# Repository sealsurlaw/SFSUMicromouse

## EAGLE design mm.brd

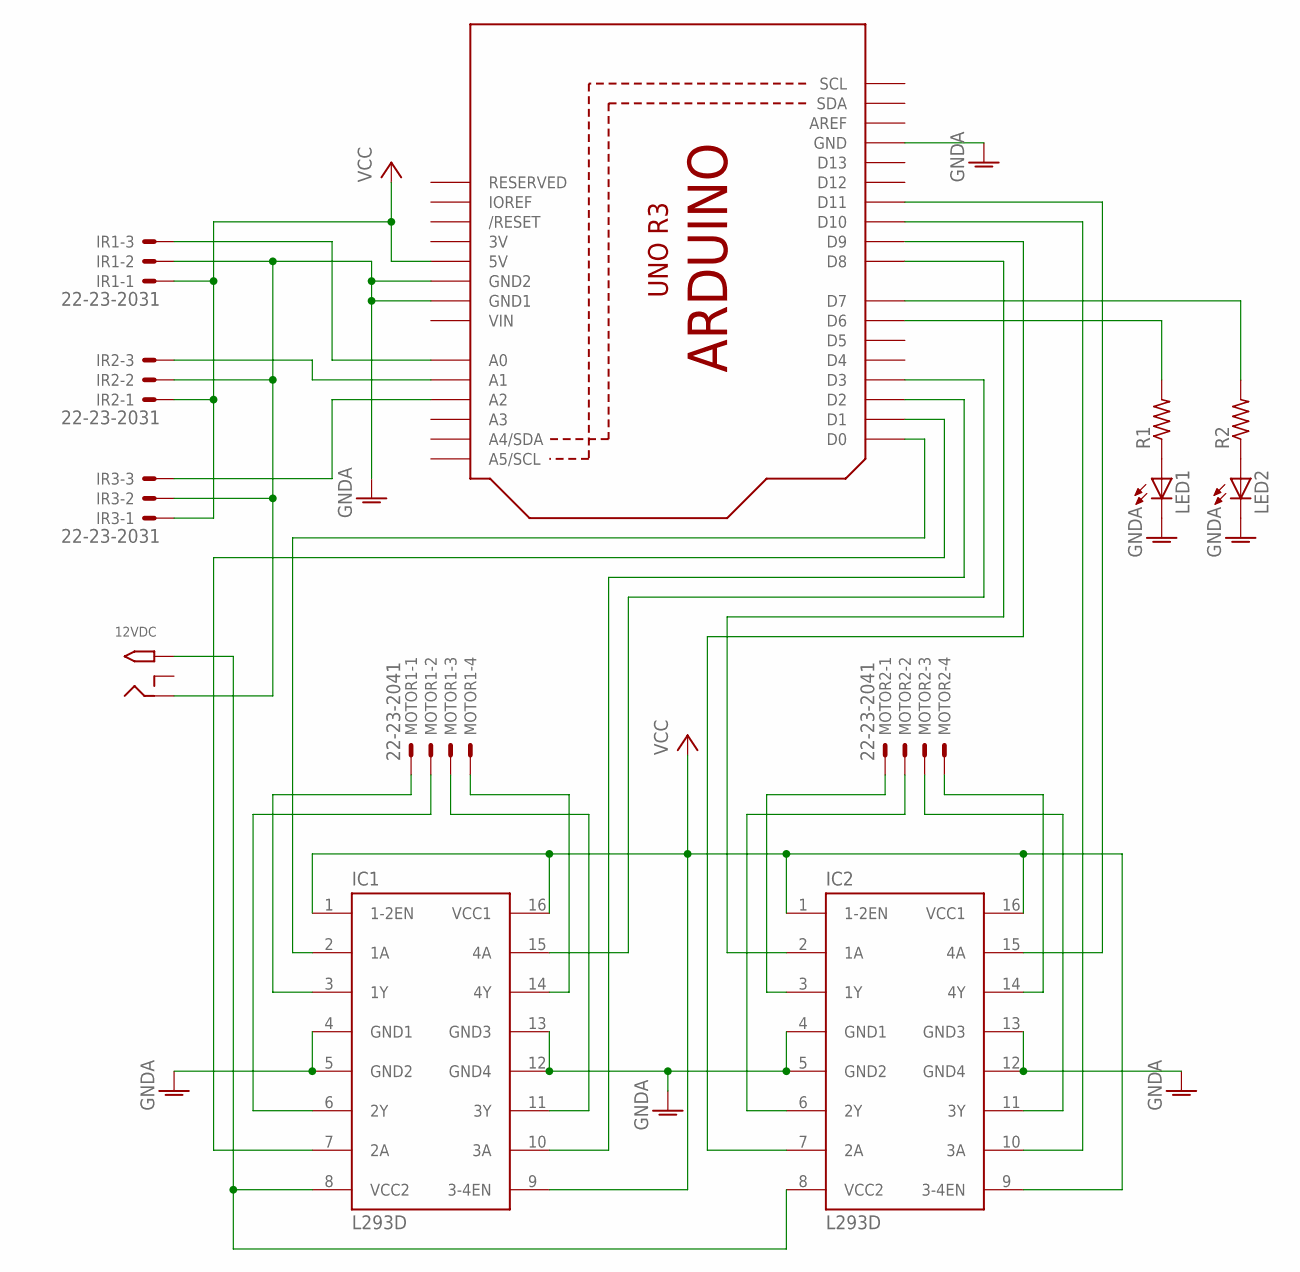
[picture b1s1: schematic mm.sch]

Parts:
12VDC: 2.1MMJACKTHM; PJ-102A
IC1, IC2: L293D; DIL16
IR1, IR2, IR3: 22-23-2031
LED1, LED2: LED3MM
MOTOR1, MOTOR2: 22-23-2041
R1, R2: R-US_0204/5; 0204/5
U1: ARDUINOR3-DIMENSION; ARDUINOR3

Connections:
3V: U1.3V
12VDC: 12VDC.TIP, IC1.8 (VCC2), IC2.8 (VCC2)
GNDA: 12VDC.RING, IC1.4 (GND1), IC1.5 (GND2), IC1.12 (GND4), IC1.13 (GND3), IC2.4 (GND1), IC2.5 (GND2), IC2.12 (GND4), IC2.13 (GND3), IR1.2, IR2.2, IR3.2, LED1.K (C), LED2.K (C), U1.GND, U1.GND1, U1.GND2
GRAY1: IC1.11 (3Y), MOTOR1.3
GRAY2: IC2.11 (3Y), MOTOR2.3
GREEN1: IC1.14 (4Y), MOTOR1.4
GREEN2: IC2.14 (4Y), MOTOR2.4
unnamed: IR1.3, U1.A0
unnamed: R1.2, U1.D6
unnamed: IR2.3, U1.A1
unnamed: IC1.2 (1A), U1.D0
unnamed: R2.2, U1.D7
unnamed: LED1.A, R1.1
unnamed: LED2.A, R2.1
unnamed: IR3.3, U1.A2
unnamed: IC1.10 (3A), U1.D2
unnamed: IC1.15 (4A), U1.D3
unnamed: IC2.2 (1A), U1.D8
unnamed: IC2.7 (2A), U1.D9
unnamed: IC2.10 (3A), U1.D10
unnamed: IC1.7 (2A), U1.D1
unnamed: IC2.15 (4A), U1.D11
RED1: IC1.3 (1Y), MOTOR1.1
RED2: IC2.3 (1Y), MOTOR2.1
VCC: IC1.1 (1-2EN), IC1.9 (3-4EN), IC1.16 (VCC1), IC2.1 (1-2EN), IC2.9 (3-4EN), IC2.16 (VCC1), IR1.1, IR2.1, IR3.1, U1.5V
VIN: U1.VIN
YELLOW1: IC1.6 (2Y), MOTOR1.2
YELLOW2: IC2.6 (2Y), MOTOR2.2

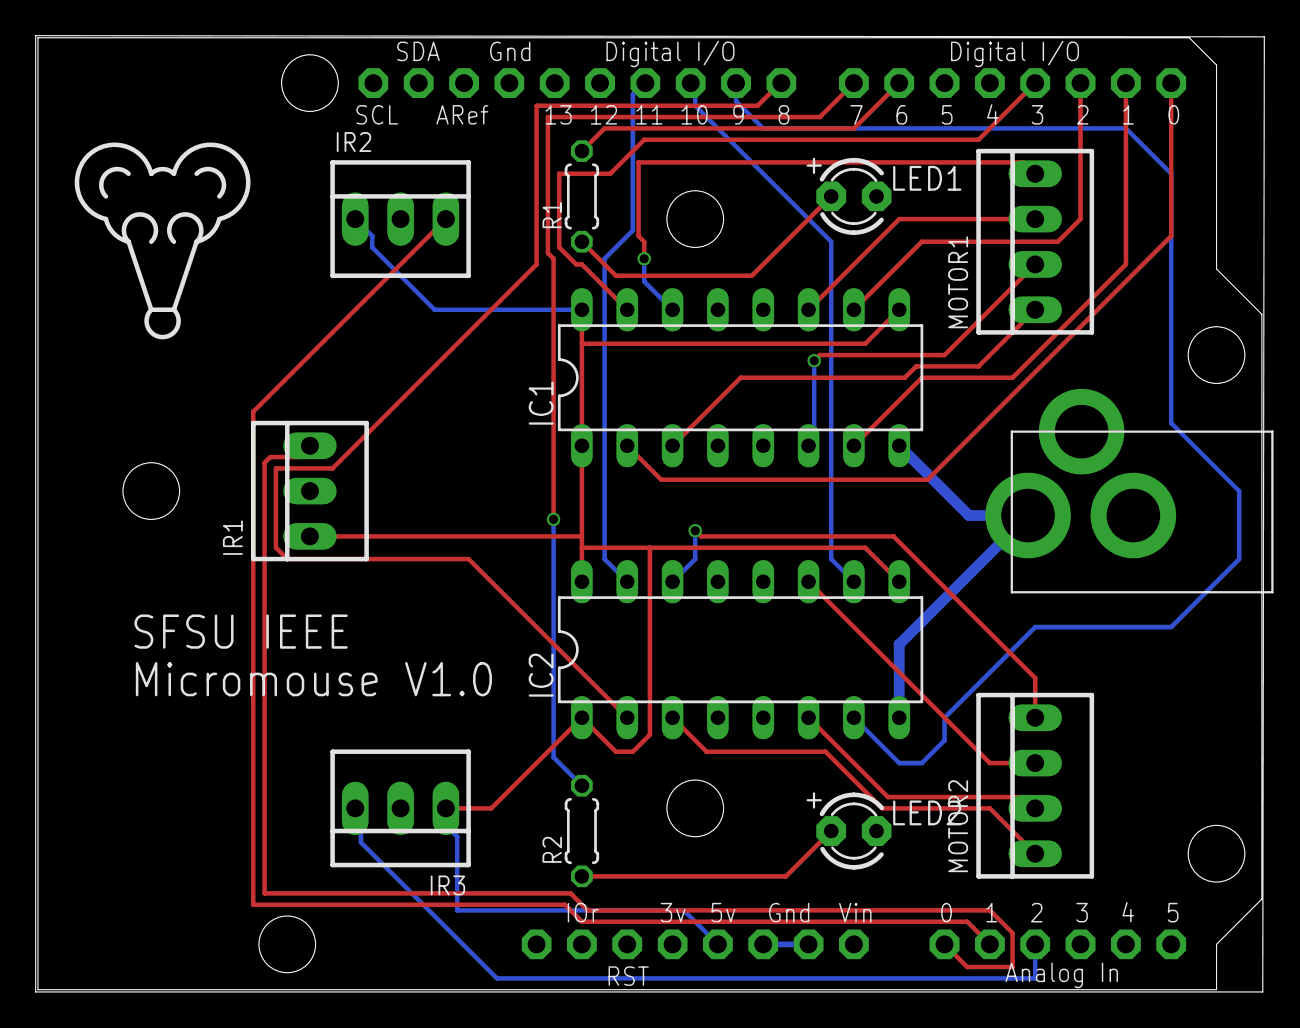
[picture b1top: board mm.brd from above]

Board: 2 copper layers, 68.8 x 53.6 mm, 13 parts (0 on the bottom side), 26 nets.

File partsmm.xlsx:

Name | Part | Datasheet | Buy
Quadruple Half H Drivers | L293D | https://cdn-shop.adafruit.com/datasheets/l293d.pdf | https://www.digikey.com/product-detail/en/stmicroelectronics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
12VDC Bipolar Stepper Motor | 324 | https://cdn-shop.adafruit.com/product-files/324/C140-A+datas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 | https://www.digikey.com/product-detail/en/adafruit-industrie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
Molex 3 Pin Male Connector | 22-23-2031 | https://www.molex.com/pdm_docs/sd/022232031_sd.pdf | https://www.digikey.com/product-detail/en/molex-llc/00222320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
Molex 3 Pin Female Connector | 22-01-3037 | https://www.molex.com/pdm_docs/sd/022013037_sd.pdf | https://www.digikey.com/product-detail/en/molex-llc/22-01-30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
Molex 4 Pin Male Connector | 22-23-2041 | https://www.molex.com/pdm_docs/sd/022232041_sd.pdf | https://www.digikey.com/product-detail/en/molex-llc/00222320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
Molex 4 Pin Female Connector | 22-01-3047 | https://www.molex.com/pdm_docs/sd/022013047_sd.pdf | https://www.digikey.com/product-detail/en/molex-llc/00220130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
IR distance sensor (2cm-15cm) | GP2Y0A51SK0F | http://www.sharp-world.com/products/device/lineup/data/pdf/d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 | https://www.digikey.com/product-detail/en/GP2Y0A51SK0F/1855-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
2.1mm DC barrel jack | PJ-102A | https://www.cui.com/product/resource/pj-102a.pdf | https://www.digikey.com/product-detail/en/cui-inc/PJ-102A/CP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
40 Pos 0.1" Headers | 61304011121 | http://katalog.we-online.de/em/datasheet/6130xx11121.pdf | https://www.digikey.com/product-detail/en/wurth-electronics-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
Sharp IR Sensor to Servo Header | 805-28995 | https://media.digikey.com/pdf/Data%20Sheets/Parallax%20PDFs/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 | https://www.digikey.com/product-detail/en/parallax-inc/805-2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
Resistor 1KOhm | CFM14JT1K00 | https://www.seielect.com/Catalog/SEI-CF_CFM.pdf | https://www.digikey.com/product-detail/en/stackpole-electron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
LED Red | SLR-342MG3F | http://www.kingbrightusa.com/images/catalog/SPEC/WP710A10LSRD.pdf | https://www.digikey.com/product-detail/en/kingbright/WP710A1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
LED Green | SLR-342MG3F | https://media.digikey.com/pdf/Data%20Sheets/Rohm%20PDFs/SLR-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 | https://www.digikey.com/product-detail/en/rohm-semiconductor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
Screw Nylon M3 | 29341 | https://www.digikey.com/product-detail/en/keystone-electroni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 | https://www.digikey.com/product-detail/en/keystone-electroni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
Screw Steel M3 | RM3X6MM 2701 |  | https://www.digikey.com/product-detail/en/apm-hexseal/RM3X6M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
Useful Resources:
https://learn.adafruit.com/adafruit-arduino-lesson-16-steppe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
https://itp.nyu.edu/physcomp/labs/motors-and-transistors/lab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

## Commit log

2018-06-12 Removed zip file
